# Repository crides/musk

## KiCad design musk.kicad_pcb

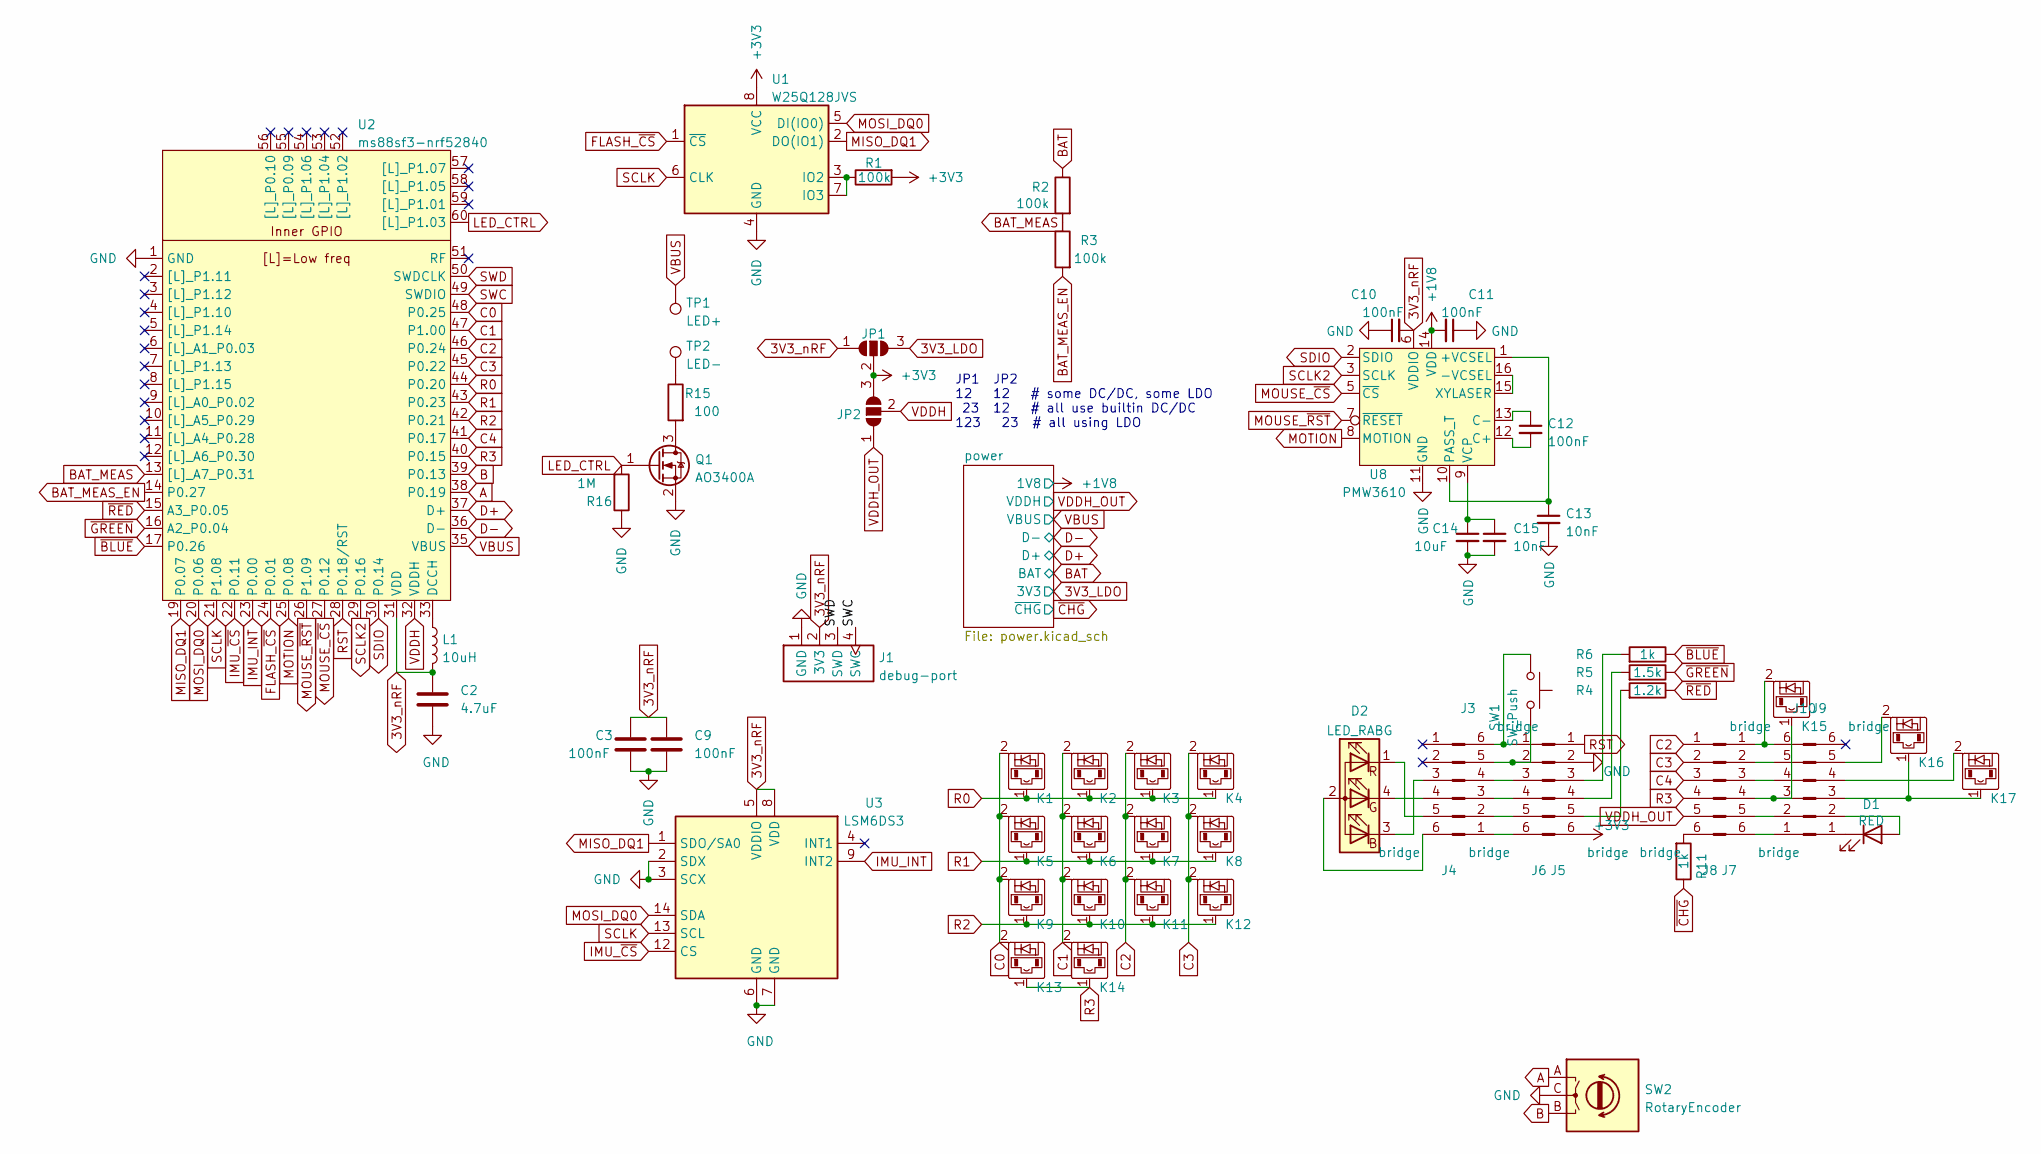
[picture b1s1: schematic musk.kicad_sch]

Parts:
C2: 4.7uF; C_0603_1608Metric
C3, C9, C10, C11, C12: 100nF; C_0603_1608Metric
C13, C15: 10nF; C_0603_1608Metric
C14: 10uF; C_0603_1608Metric
D1: RED; LED_0805_2012Metric
D2: LED_RABG; LED_ASMB-KTF0-0A306
J1: debug-port; debug-port-single-side
J3, J4, J5, J6, J7, J8, J9, J10: bridge
JP1, JP2: left right or all; SolderJumper-3_P1.3mm_Open_RoundedPad1.0x1.5mm
K1, K5, K9: diode-choc; pg1232-DHCR; lcsc-part C64898
K2, K6, K10, K14, K15, K16, K17: diode-choc; pg1232-DHC; lcsc-part C64898
K3, K7, K11: diode-choc; pg1232-DHCL; lcsc-part C64898
K4, K8, K12: diode-choc; pg1232-DHCN; lcsc-part C64898
K13: diode-choc; pg1232-DHC
L1: 10uH; L_0603_1608Metric
Q1: AO3400A; SOT-23
R1, R2, R3: 100k; R_0603_1608Metric
R4: 1.2k; R_0603_1608Metric
R5: 1.5k; R_0603_1608Metric
R6, R11: 1k; R_0603_1608Metric
R15: 100; R_0603_1608Metric
R16: 1M; R_0603_1608Metric
SW1: SW_Push; SW_SPST_TL3342
SW2: RotaryEncoder; EC10E
TP1: LED+; TestPoint_THTPad_D2.0mm_Drill1.0mm
TP2: LED-; TestPoint_THTPad_D2.0mm_Drill1.0mm
U1: W25Q128JVS; SOIC-8_5.23x5.23mm_P1.27mm
U2: ms88sf3-nrf52840; ms88sf3
U3: LSM6DS3; LGA-14_3x2.5mm_P0.5mm_LayoutBorder3x4y
U8: PMW3610

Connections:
3V3_LDO: JP1.3 (B); also elsewhere on the board
3V3_nRF: C2.1, C3.1, C9.1, C10.2, J1.2 (3V3), JP1.1 (A), L1.2, U2.31 (VDD), U3.5 (VDDIO), U3.8 (VDD), U8.6 (VDDIO)
+1V8: C11.2, U8.14 (VDD); also elsewhere on the board
+3V3: J5.6, JP1.2 (C), JP2.3 (B), R1.2, U1.8 (VCC)
A: SW2.A, U2.38 (P0.19)
B: SW2.B, U2.39 (P0.13)
BAT: R2.1; also elsewhere on the board
BAT_MEAS: R2.2, R3.1, U2.13 ([L]_A7_P0.31)
BAT_MEAS_EN: R3.2, U2.14 (P0.27)
C0: K1.2, K5.2, K9.2, K13.2, U2.48 (P0.25)
C1: K2.2, K6.2, K10.2, K14.2, U2.47 (P1.00)
C2: J8.1, K3.2, K7.2, K11.2, U2.46 (P0.24)
C3: J8.2, K4.2, K8.2, K12.2, U2.45 (P0.22)
C4: J8.3, U2.41 (P0.17)
D+: U2.37 (D+); also elsewhere on the board
D-: U2.36 (D-); also elsewhere on the board
FLASH_~CS: U1.1 (~CS), U2.24 (P0.01)
GND: C2.2, C3.2, C9.2, C10.1, C11.1, C13.2, C14.2, C15.2, J1.1 (GND), J5.2, Q1.2 (S), R16.1, SW2.C, U1.4 (GND), U2.1 (GND), U2.18 (GND), U2.34 (GND), U2.61 (GND), U2.62 (GND), U2.63 (GND), U2.64 (GND), U3.2 (SDX), U3.3 (SCX), U3.6 (GND), U3.7 (GND), U8.11 (GND); also elsewhere on the board
IMU_INT: U2.23 (P0.00), U3.9 (INT2)
IMU_~CS: U2.22 (P0.11), U3.12 (CS)
MISO_DQ1: U1.2 (DO(IO1)), U2.19 (P0.07), U3.1 (SDO/SA0)
MOSI_DQ0: U1.5 (DI(IO0)), U2.20 (P0.06), U3.14 (SDA)
MOTION: U2.25 (P0.08), U8.8 (MOTION)
MOUSE_~CS: U2.27 (P0.12), U8.5 (~CS)
MOUSE_~RST: U2.26 (P1.09), U8.7 (~RESET)
unnamed: C12.1, U8.13 (C-)
unnamed: C12.2, U8.12 (C+)
unnamed: C13.1, U8.1 (+VCSEL), U8.10 (PASS_T)
unnamed: C14.1, C15.1, U8.9 (VCP)
unnamed: D1.1 (K), J9.1
unnamed: D1.2 (A), J9.2
unnamed: D2.1 (RK), J4.5
unnamed: D2.2 (A), J4.6
unnamed: D2.3 (BK), J4.3
unnamed: D2.4 (GK), J4.4
unnamed: J3.1, J6.6
unnamed: J3.2, J6.5
unnamed: J3.3, J6.4
unnamed: J3.4, J6.3
unnamed: J3.5, J6.2, SW1.2
unnamed: J3.6, J6.1, SW1.1
unnamed: J5.3, R6.2
unnamed: J5.4, R5.2
unnamed: J5.5, R4.2
unnamed: J8.6, R11.2
unnamed: J9.3, K16.1, K17.1
unnamed: J9.4, K17.2
unnamed: J9.5, K16.2
unnamed: J7.6, J10.1
unnamed: J7.5, J10.2
unnamed: J7.4, J10.3, K15.1
unnamed: J7.3, J10.4
unnamed: J7.2, J10.5
unnamed: J7.1, J10.6, K15.2
unnamed: L1.1, U2.33 (DCCH)
unnamed: Q1.3 (D), R15.2
unnamed: R1.1, U1.3 (IO2), U1.7 (IO3)
unnamed: R15.1, TP2.1
unnamed: U8.15 (XYLASER), U8.16 (-VCSEL)
R0: K1.1, K2.1, K3.1, K4.1, U2.44 (P0.20)
R1: K5.1, K6.1, K7.1, K8.1, U2.43 (P0.23)
R2: K9.1, K10.1, K11.1, K12.1, U2.42 (P0.21)
R3: J8.4, K13.1, K14.1, U2.40 (P0.15)
RST: J5.1, U2.28 (P0.18/RST)
SCLK: U1.6 (CLK), U2.21 (P1.08), U3.13 (SCL)
SCLK2: U2.29 (P0.16), U8.3 (SCLK)
SDIO: U2.30 (P0.14), U8.2 (SDIO)
SWC: J1.4 (SWC), U2.49 (SWDIO)
SWD: J1.3 (SWD), U2.50 (SWDCLK)
VBUS: TP1.1, U2.35 (VBUS); also elsewhere on the board
VDDH: JP2.2 (C), U2.32 (VDDH)
VDDH_OUT: J8.5, JP2.1 (A); also elsewhere on the board
~BLUE: R6.1, U2.17 (P0.26)
~CHG: R11.1; also elsewhere on the board
~GREEN: R5.1, U2.16 (A2_P0.04)
~LED_OFF: Q1.1 (G), R16.2, U2.60 ([L]_P1.03)
~RED: R4.1, U2.15 (A3_P0.05)

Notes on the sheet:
JP1 JP2 12 12 # some DC/DC, some LDO 23 12 # all use builtin DC/DC 123 23 # all using LDO

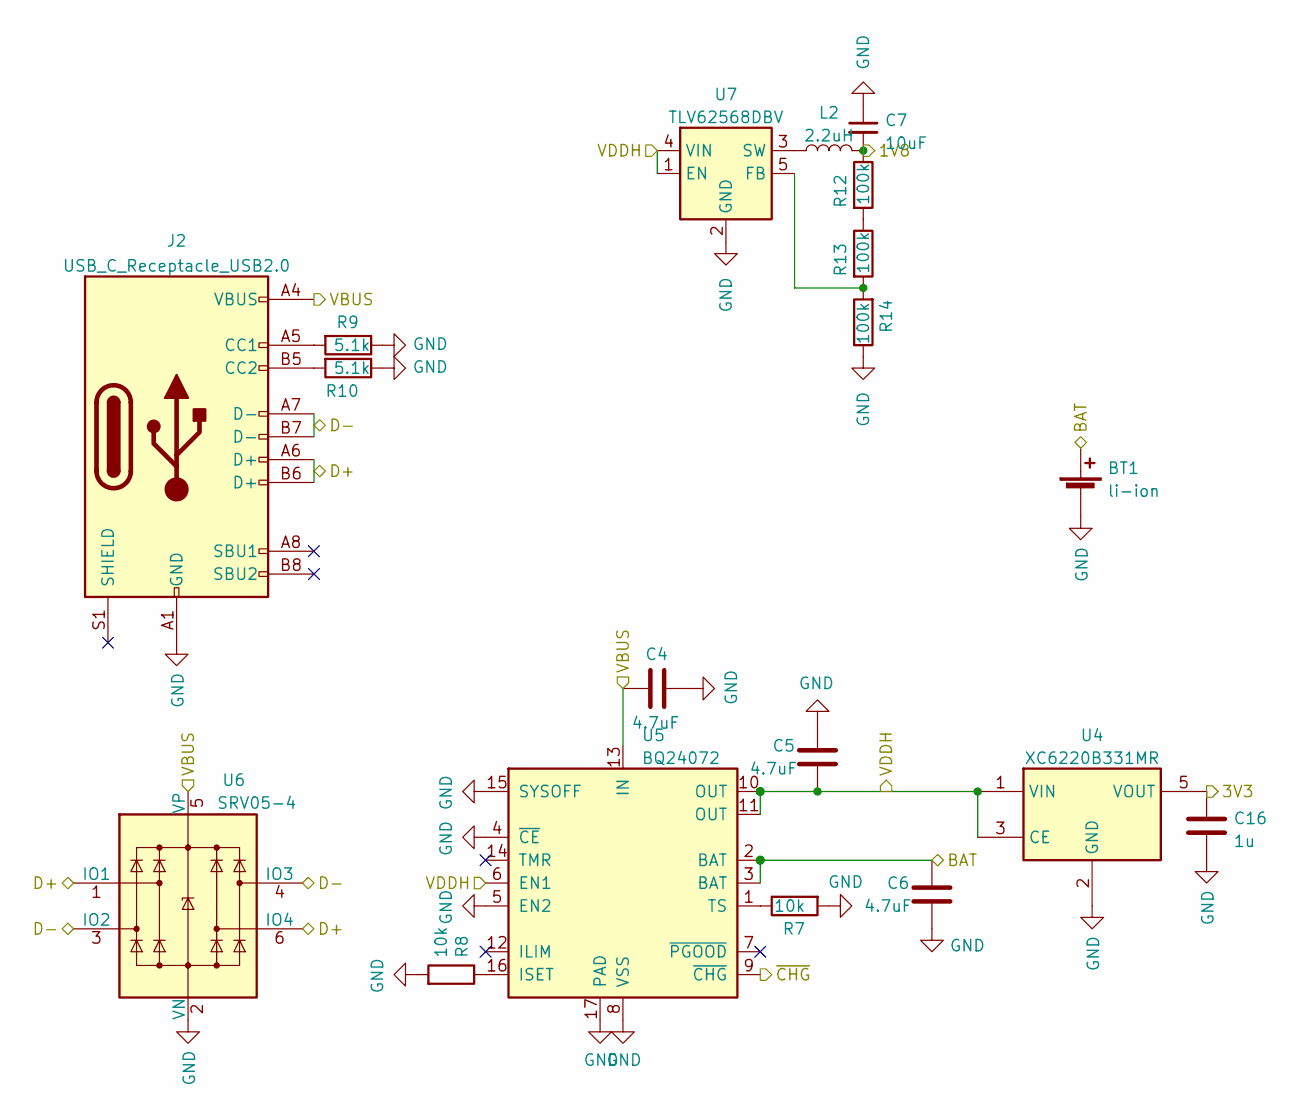
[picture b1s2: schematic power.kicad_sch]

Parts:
BT1: li-ion; JST_PH_S2B-PH-SM4-TB_1x02-1MP_P2.00mm_Horizontal
C4, C5, C6: 4.7uF; C_0603_1608Metric
C7: 10uF; C_0603_1608Metric
C16: 1u; C_0603_1608Metric
J2: USB_C_Receptacle_USB2.0; USB_C_Receptacle_HRO_TYPE-C-31-M-12
L2: 2.2uH; L_1008_2520Metric; lcsc-part C354533
R7, R8: 10k; R_0603_1608Metric
R9, R10: 5.1k; R_0603_1608Metric
R12, R13, R14: 100k; R_0603_1608Metric
U4: XC6220B331MR; SOT-23-5; lcsc-part C5446
U5: BQ24072; VQFN-16-1EP_3x3mm_P0.5mm_EP1.68x1.68mm_ThermalVias
U6: SRV05-4; SOT-23-6
U7: TLV62568DBV; SOT-23-5; lcsc-part C163219

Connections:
3V3_LDO: C16.1, U4.5 (VOUT); also elsewhere on the board
+1V8: C7.2, L2.2, R12.1; also elsewhere on the board
BAT: BT1.1 (+), C6.1, U5.2 (BAT), U5.3 (BAT); also elsewhere on the board
D+: J2.A6 (D+), J2.B6 (D+), U6.1 (IO1), U6.6 (IO4); also elsewhere on the board
D-: J2.A7 (D-), J2.B7 (D-), U6.3 (IO2), U6.4 (IO3); also elsewhere on the board
GND: BT1.2 (-), C4.2, C5.1, C6.2, C7.1, C16.2, J2.A1 (GND), J2.A12 (GND), J2.B1 (GND), J2.B12 (GND), R7.2, R8.2, R9.1, R10.1, R14.1, U4.2 (GND), U5.4 (~CE), U5.5 (EN2), U5.8 (VSS), U5.15 (SYSOFF), U5.17 (PAD), U6.2 (VN), U7.2 (GND); also elsewhere on the board
unnamed: J2.A5 (CC1), R9.2
unnamed: J2.B5 (CC2), R10.2
unnamed: L2.1, U7.3 (SW)
unnamed: R7.1, U5.1 (TS)
unnamed: R8.1, U5.16 (ISET)
unnamed: R12.2, R13.1
unnamed: R13.2, R14.2, U7.5 (FB)
VBUS: C4.1, J2.A4 (VBUS), J2.A9 (VBUS), J2.B4 (VBUS), J2.B9 (VBUS), U5.13 (IN), U6.5 (VP); also elsewhere on the board
VDDH_OUT: C5.2, U4.1 (VIN), U4.3 (CE), U5.6 (EN1), U5.10 (OUT), U5.11 (OUT), U7.1 (EN), U7.4 (VIN); also elsewhere on the board
~CHG: U5.9 (~CHG); also elsewhere on the board

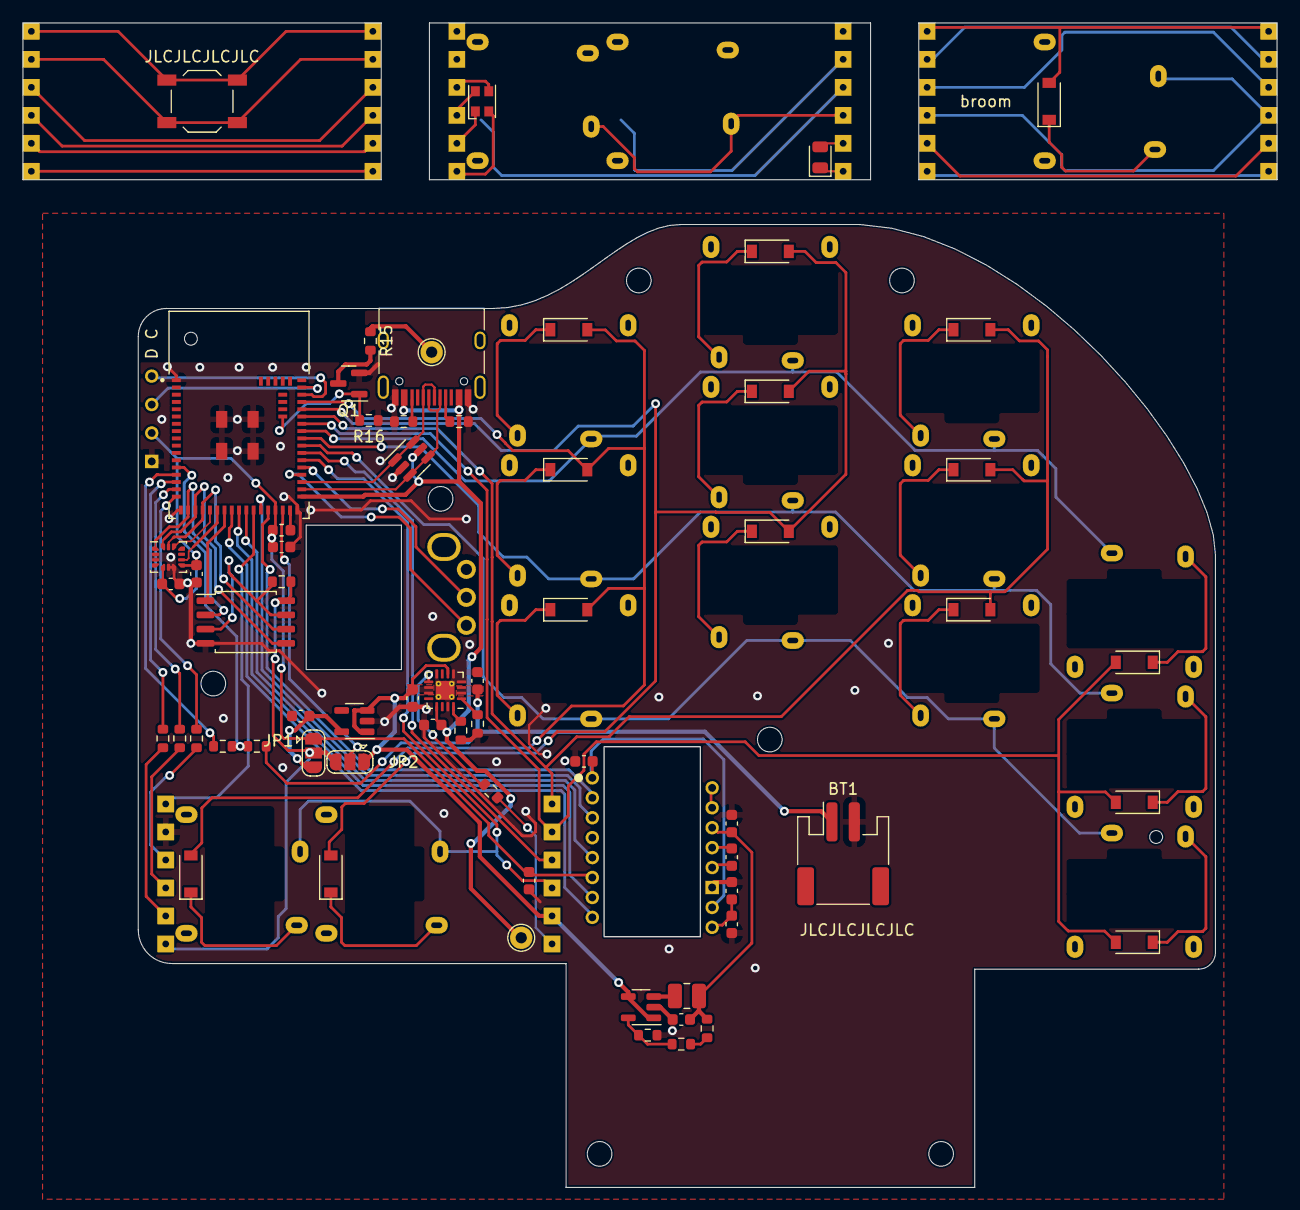
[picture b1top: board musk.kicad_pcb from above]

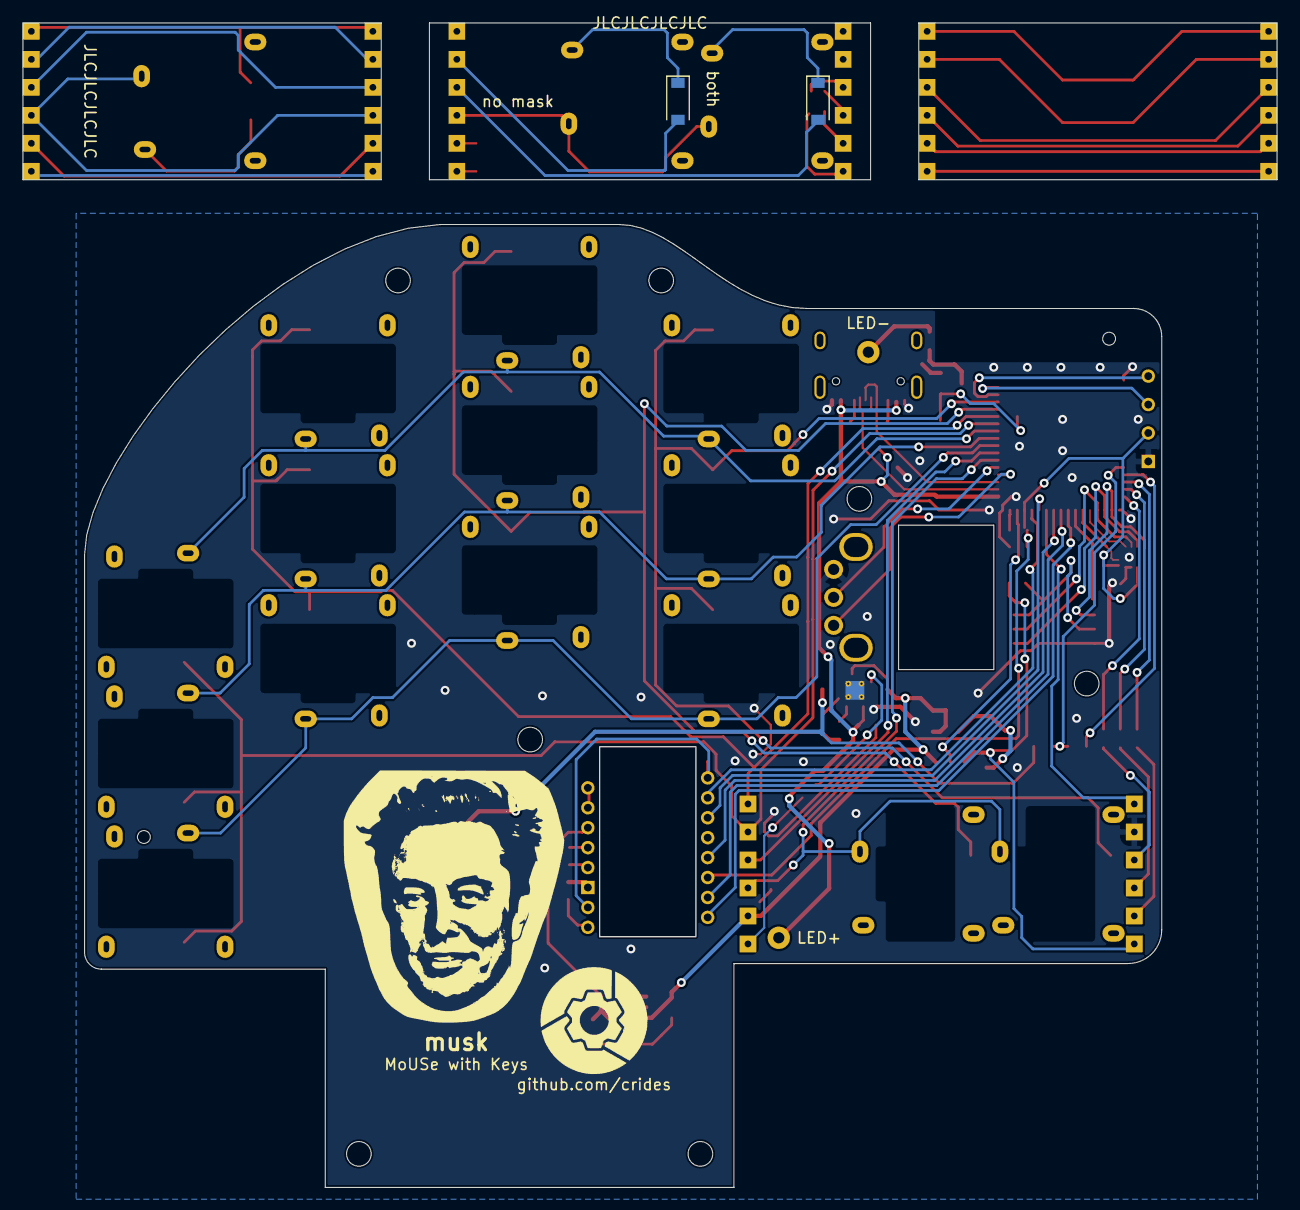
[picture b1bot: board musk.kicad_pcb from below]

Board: 2 copper layers, 112.0 x 104.0 mm, 77 parts (5 on the bottom side), 84 nets.

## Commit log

2023-01-05 new start
2023-01-05 Initial PCB version
2023-01-05 Pending
2023-01-05 Switch thumb-thumb to go thru
2023-01-05 backup
2023-01-05 rename
2023-01-05 no screen
2023-01-05 routed with encoder model
2023-01-05 done
2023-01-05 routed
2023-01-05 scroll wheel + constant current charger
2023-01-05 5 thumb cluster
2023-01-05 case
2023-01-08 hotswap choc mini
2023-01-16 wheel holder end
2023-01-19 swap bms and reg
2023-02-01 adjust position
2023-02-01 add groove for nOOd
2023-02-01 fabed
